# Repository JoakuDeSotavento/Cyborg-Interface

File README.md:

# InCY, INTERFACE CYBORG

## aka Jakinator

## physical interface for transforming the human body in the interface itself

## Team

### JOAQUÍN ROBERTO DÍAZ DURÁN

> PhD Researcher at Universidad Carlos III de Madrid

### MARTA TIMÓN

> M.C.S.

### PEDRO LÓPEZ

> Ing. En Electrónica

> Joakinator beta

Key Words
Interfaz corporal, Arte Ciborg, Performance, Propiocepción, Adaptar la tecnología al artista, dialogo con el otro, HCI

Joakinator is an interaface devoted to convert the languaje and signs of the human body in the interface itslef. The idea behind Joakinator is giving direct control of the multimedia elements to the artist, but this elements are not just controlled by the artist, in fact the artist also receive cues from the system. Joakinator will be a creative assistant in the creation proces of a performance.

## Skematics

## Code

## CAD DESIGN

## Getting started

Protocolo de conexión Joakinator

1. Abrir el hostspot del teléfono
2. Conectar las computadoras al hostspot y revisar su dirección IP
3. Configurar el archivo secrets.h y la parte de las direcciones IP en el programa de Arduino
4. Cargar las modificaciones al Arduino del Joakinator
5. Desconectar el cable USB y colocar las baterías. Esperar a que el led amarillo se encienda, eso significa que se ha conectado a la WLAN
6. Abrir el programa de Processing y ejecutarlo
   a. Barras blancas son las señales del Joakinator
   b. Las barras naranjas son las señales del Wekinator
7. Ver que las barras blancas vibren, si no es así resetear el Joakinator
8. Abrir Wekinator Input_helper
   a. Comprobar los puertos
9. Abrir Wekinator
   a. Comprobar los puertos
10. Abrir MAX/MSP

Protocolo de montaje del Joakinator en cuerpo

1. Seleccionar el musculo sobre el que se montara el electrodo
2. Identificar la parte central del musculo y la parte distal
3. Limpiar con alcohol o agua oxigenada las tres áreas donde se colocarán los electrodos
4. Colocar los tres electrodos en sus posiciones
   a. Rojo es la referencia
   b. Amarillo es el middle muscle
   c. Verde es el end muscle
5. Colocar la referencia general, el electrodo de un solo plug
6. Colocar los cables con los sensores flexiforce
7. Calibrar la sensibilidad de los flexiforce con los knobs
   Nota. Los Jack del lado grande del Joakinator son para los electrodos y los que están con lo knobs son para los flexiforce

## Performance using Joakinator

<div align="center">
  
</div>

> El equilibrio reside en 3 puntos
> Festival Ctrl Art Supr, Madrid, Marzo, 2019

- [Link](https://arterobotico.com/el-equilibrio-reside-en-3-puntos/)

<div align="center">
  
</div>

> Interfaz Cyborg para reflexionar la tecnología
> Encuentro Si fuese Tú, Facultad de Bellas Artes de Cuenca, UCLM, Abril, 2019

- [Link](https://arterobotico.com/interfaz-ciborg-para-reflexionar-la-tecnologia/)

## Agradecimientos

- Suported by BODYinTRANSIT Sensory-driven Body Transformation Experiences On-the-move, MagicShoes and i_mBODY Lab at UC3M.
- With the collaboration of FUZZYGAB.4. UCLM
- Project developed with the funding of CONACYT-FINBA. México; Medialab-Matadero. España."

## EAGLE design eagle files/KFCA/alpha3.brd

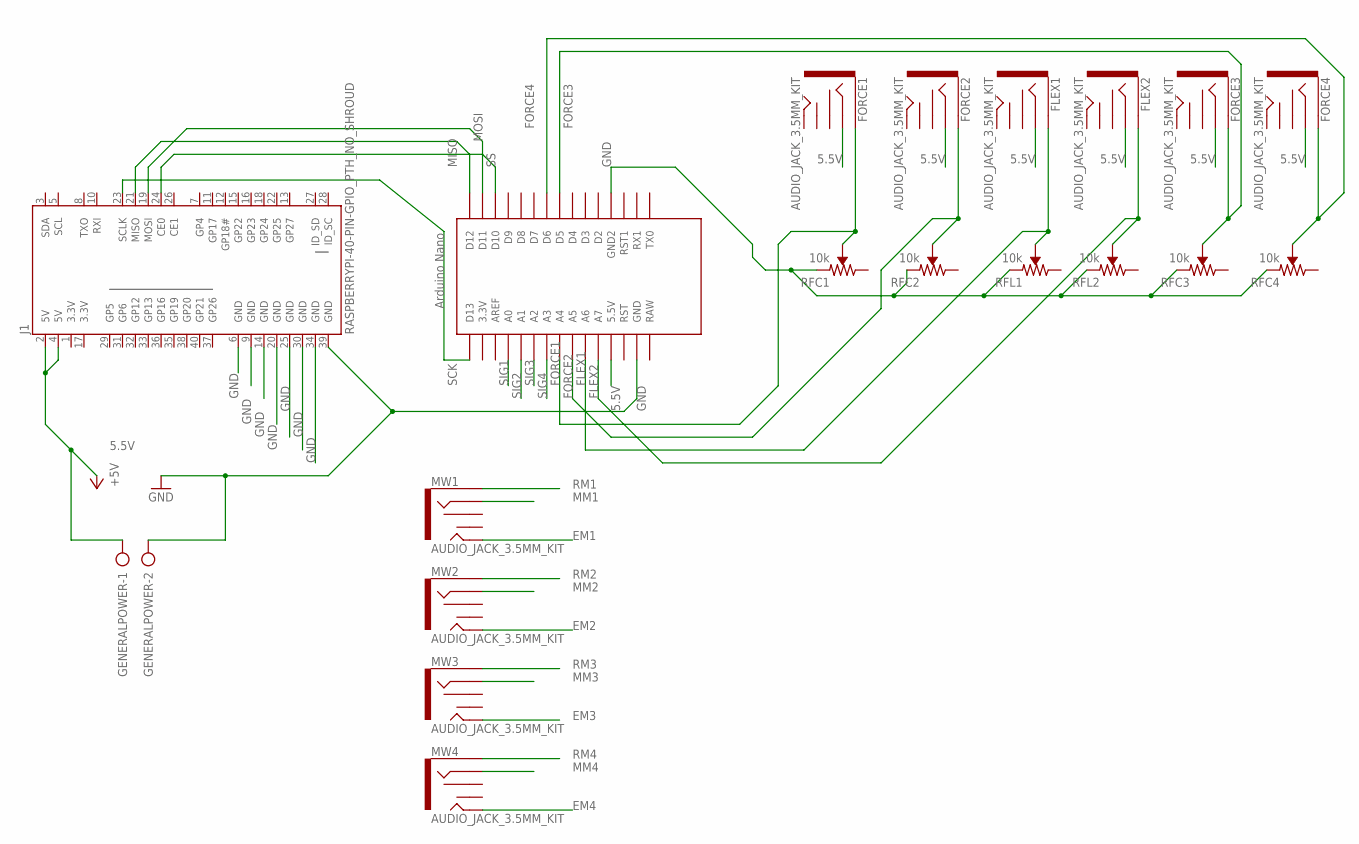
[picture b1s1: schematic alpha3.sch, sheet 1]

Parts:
FLEX1, FLEX2: AUDIO_JACK_3.5MM_KIT; AUDIO-JACK-KIT
FORCE1, FORCE2, FORCE3, FORCE4: AUDIO_JACK_3.5MM_KIT; AUDIO-JACK-KIT
GENERALPOWER: AK500/2
J1: RASPBERRYPI-40-PIN-GPIO_PTH_NO_SHROUD; 2X20
MW1, MW2, MW3, MW4: AUDIO_JACK_3.5MM_KIT; AUDIO-JACK-KIT
RFC1, RFC2, RFC3, RFC4: 10k; TRIMPOT-PTH-3386U
RFL1, RFL2: 10k; TRIMPOT-PTH-3386U
U$1: NANO

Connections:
3.3V: J1.1 (3.3V), J1.17 (3.3V)
5.5V: FLEX1.RING, FLEX2.RING, FORCE1.RING, FORCE2.RING, FORCE3.RING, FORCE4.RING, GENERALPOWER.1, J1.2 (5V), J1.4 (5V), U$1.5V (5.5V); also elsewhere on the board
EM1: MW1.TIP; also elsewhere on the board
EM2: MW2.TIP; also elsewhere on the board
EM3: MW3.TIP; also elsewhere on the board
EM4: MW4.TIP; also elsewhere on the board
FLEX1: FLEX1.SLEEVE, RFL1.2 (WIPER), U$1.A6
FLEX2: FLEX2.SLEEVE, RFL2.2 (WIPER), U$1.A7
FORCE1: FORCE1.SLEEVE, RFC1.2 (WIPER), U$1.A4
FORCE2: FORCE2.SLEEVE, RFC2.2 (WIPER), U$1.A5
FORCE3: FORCE3.SLEEVE, RFC3.2 (WIPER), U$1.D5
FORCE4: FORCE4.SLEEVE, RFC4.2 (WIPER), U$1.D6
GND: GENERALPOWER.2, J1.6 (GND), J1.9 (GND), J1.14 (GND), J1.20 (GND), J1.25 (GND), J1.30 (GND), J1.34 (GND), J1.39 (GND), RFC1.1 (CCW), RFC2.1 (CCW), RFC3.1 (CCW), RFC4.1 (CCW), RFL1.1 (CCW), RFL2.1 (CCW), U$1.GND, U$1.GND1 (GND2); also elsewhere on the board
MISO: J1.21 (MISO), U$1.D12
MM1: MW1.RING; also elsewhere on the board
MM2: MW2.RING; also elsewhere on the board
MM3: MW3.RING; also elsewhere on the board
MM4: MW4.RING; also elsewhere on the board
MOSI: J1.19 (MOSI), U$1.D11
RM1: MW1.SLEEVE; also elsewhere on the board
RM2: MW2.SLEEVE; also elsewhere on the board
RM3: MW3.SLEEVE; also elsewhere on the board
RM4: MW4.SLEEVE; also elsewhere on the board
SCK: J1.23 (SCLK), U$1.D13
SIG1: U$1.A0; also elsewhere on the board
SIG2: U$1.A1; also elsewhere on the board
SIG3: U$1.A2; also elsewhere on the board
SIG4: U$1.A3; also elsewhere on the board
SS: J1.24 (CE0), U$1.D10

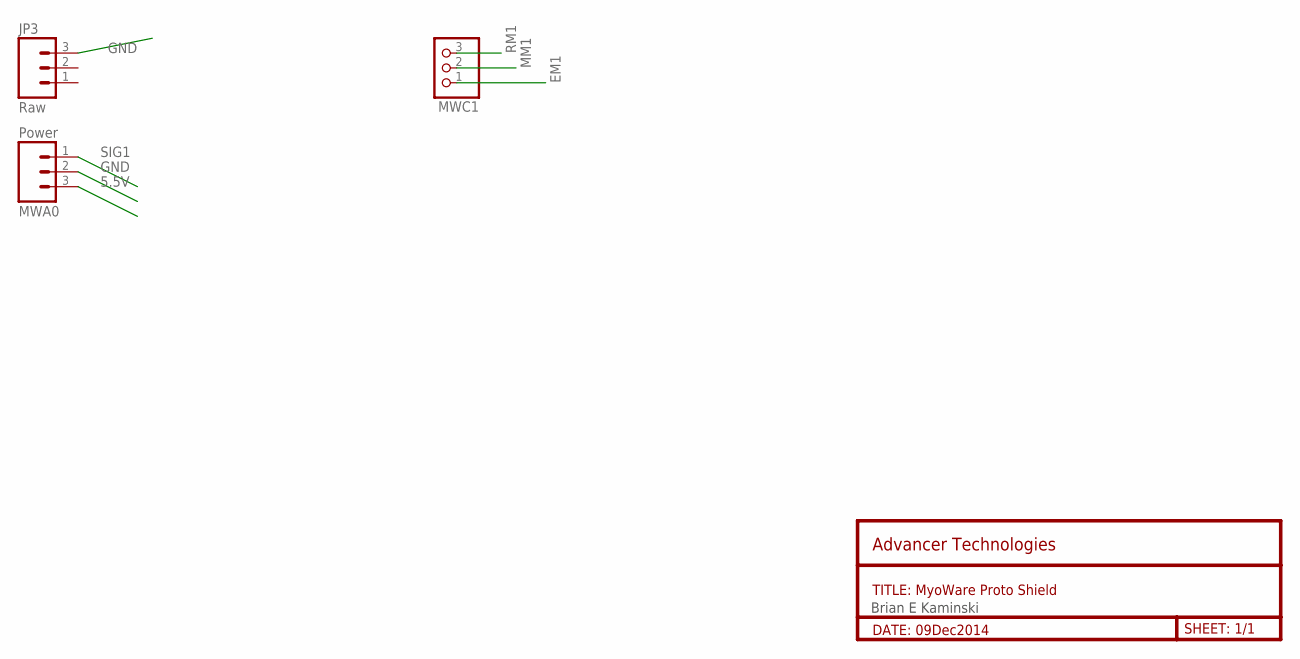
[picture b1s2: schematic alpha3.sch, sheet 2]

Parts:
JP3: Raw; 1X03_NO_SILK
MWA0: Power; 1X03_NO_SILK
MWC1: PINHD-1X3; 1X03

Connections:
5.5V: MWA0.3; also elsewhere on the board
EM1: MWC1.1; also elsewhere on the board
GND: JP3.3, MWA0.2; also elsewhere on the board
MM1: MWC1.2; also elsewhere on the board
RM1: MWC1.3; also elsewhere on the board
SIG1: MWA0.1; also elsewhere on the board

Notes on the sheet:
Brian E Kaminski
TITLE: MyoWare Proto Shield
DATE: 09Dec2014
SHEET: 1/1
Advancer Technologies

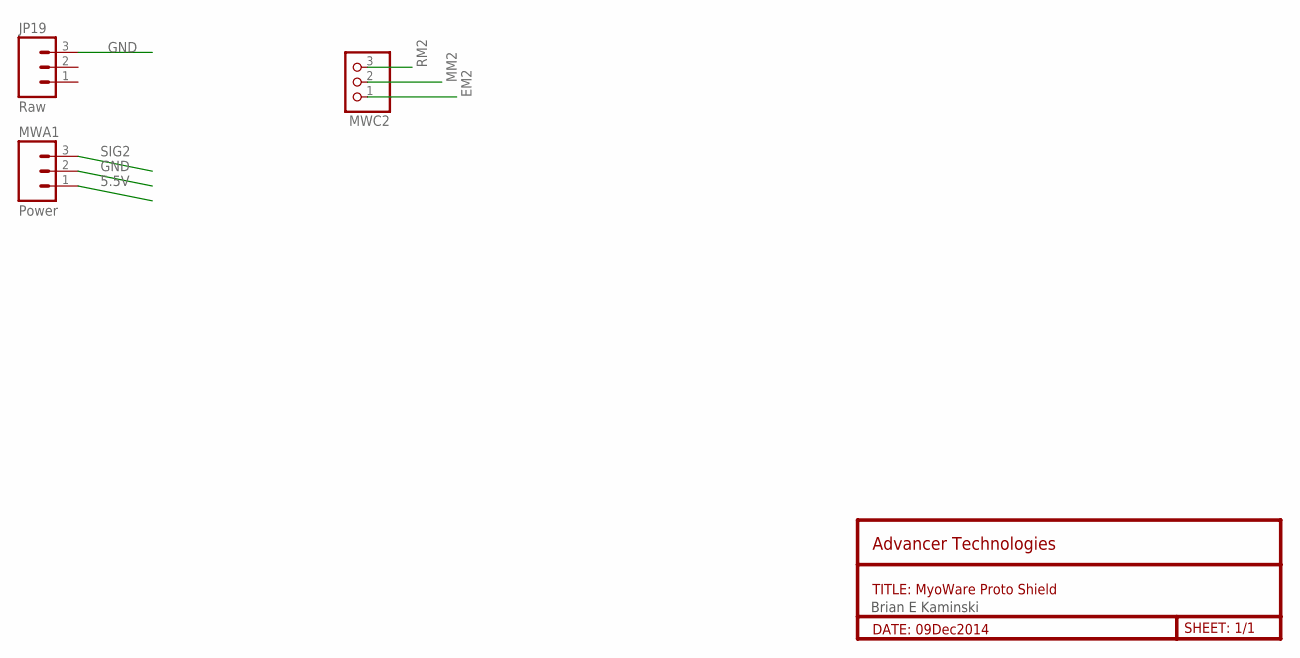
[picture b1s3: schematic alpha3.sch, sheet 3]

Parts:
JP19: Raw; 1X03_NO_SILK
MWA1: Power; 1X03_NO_SILK
MWC2: PINHD-1X3; 1X03

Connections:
5.5V: MWA1.1; also elsewhere on the board
EM2: MWC2.1; also elsewhere on the board
GND: JP19.3, MWA1.2; also elsewhere on the board
MM2: MWC2.2; also elsewhere on the board
RM2: MWC2.3; also elsewhere on the board
SIG2: MWA1.3; also elsewhere on the board

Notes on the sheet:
Brian E Kaminski
TITLE: MyoWare Proto Shield
DATE: 09Dec2014
SHEET: 1/1
Advancer Technologies

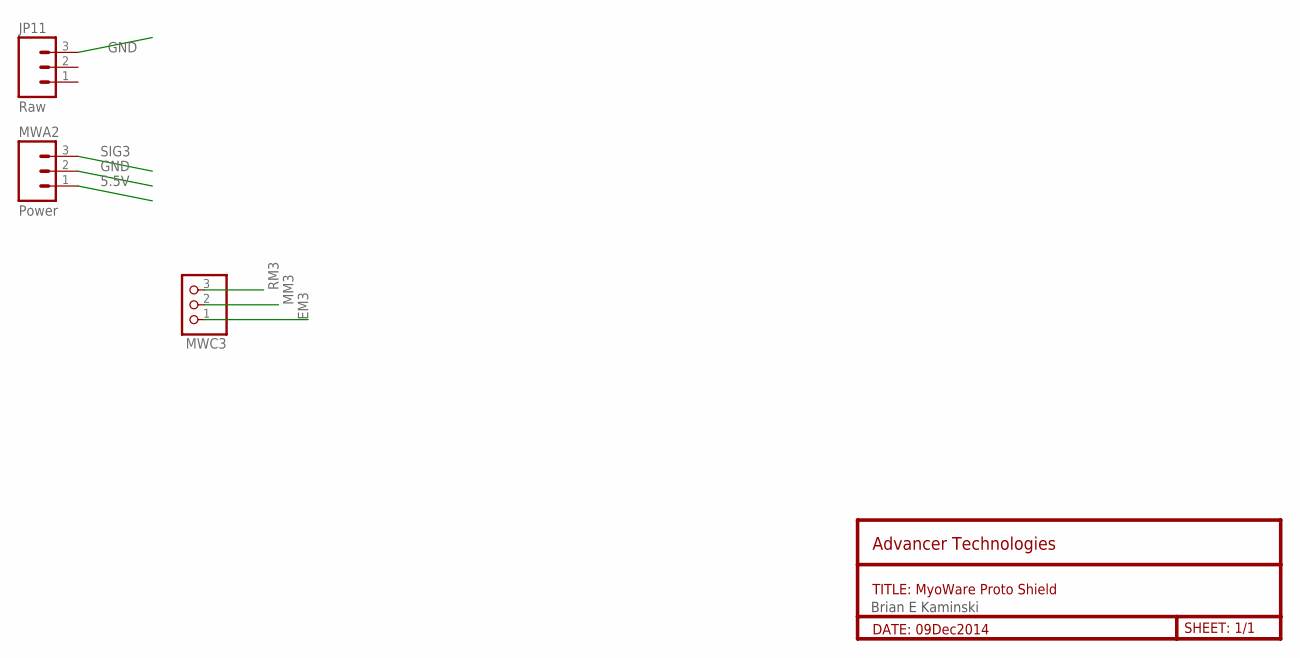
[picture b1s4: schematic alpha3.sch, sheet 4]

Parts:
JP11: Raw; 1X03_NO_SILK
MWA2: Power; 1X03_NO_SILK
MWC3: PINHD-1X3; 1X03

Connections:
5.5V: MWA2.1; also elsewhere on the board
EM3: MWC3.1; also elsewhere on the board
GND: JP11.3, MWA2.2; also elsewhere on the board
MM3: MWC3.2; also elsewhere on the board
RM3: MWC3.3; also elsewhere on the board
SIG3: MWA2.3; also elsewhere on the board

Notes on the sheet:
Brian E Kaminski
TITLE: MyoWare Proto Shield
DATE: 09Dec2014
SHEET: 1/1
Advancer Technologies

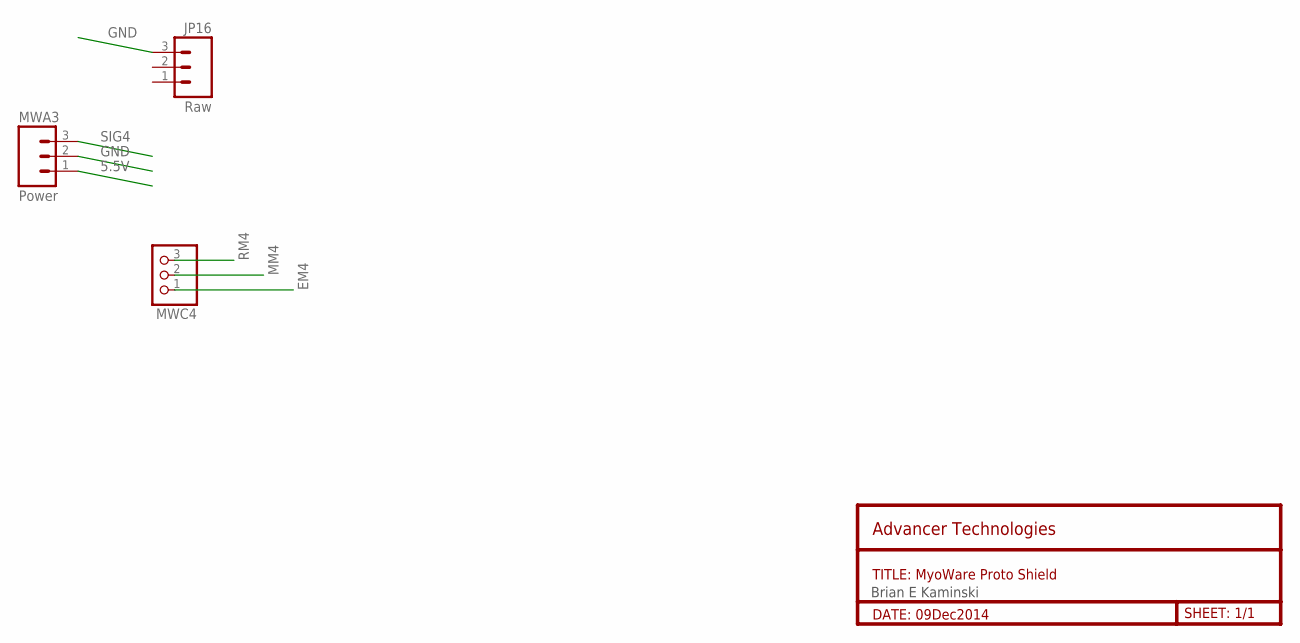
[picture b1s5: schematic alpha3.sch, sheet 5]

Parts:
JP16: Raw; 1X03_NO_SILK
MWA3: Power; 1X03_NO_SILK
MWC4: PINHD-1X3; 1X03

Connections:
5.5V: MWA3.1; also elsewhere on the board
EM4: MWC4.1; also elsewhere on the board
GND: JP16.3, MWA3.2; also elsewhere on the board
MM4: MWC4.2; also elsewhere on the board
RM4: MWC4.3; also elsewhere on the board
SIG4: MWA3.3; also elsewhere on the board

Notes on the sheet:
Brian E Kaminski
TITLE: MyoWare Proto Shield
DATE: 09Dec2014
SHEET: 1/1
Advancer Technologies

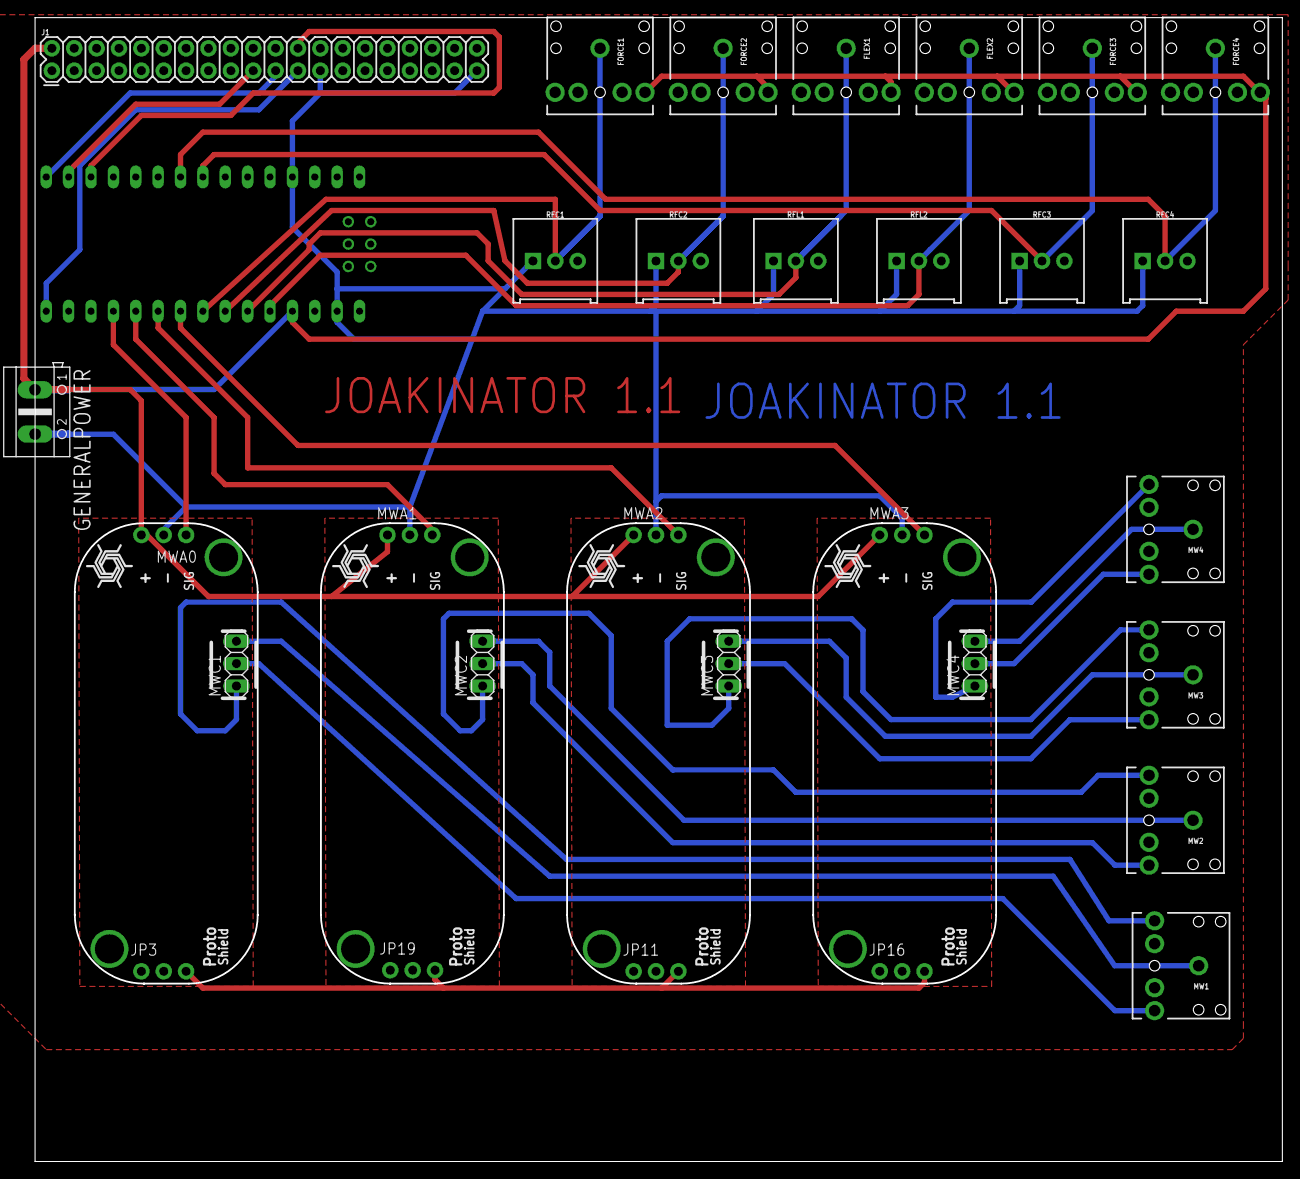
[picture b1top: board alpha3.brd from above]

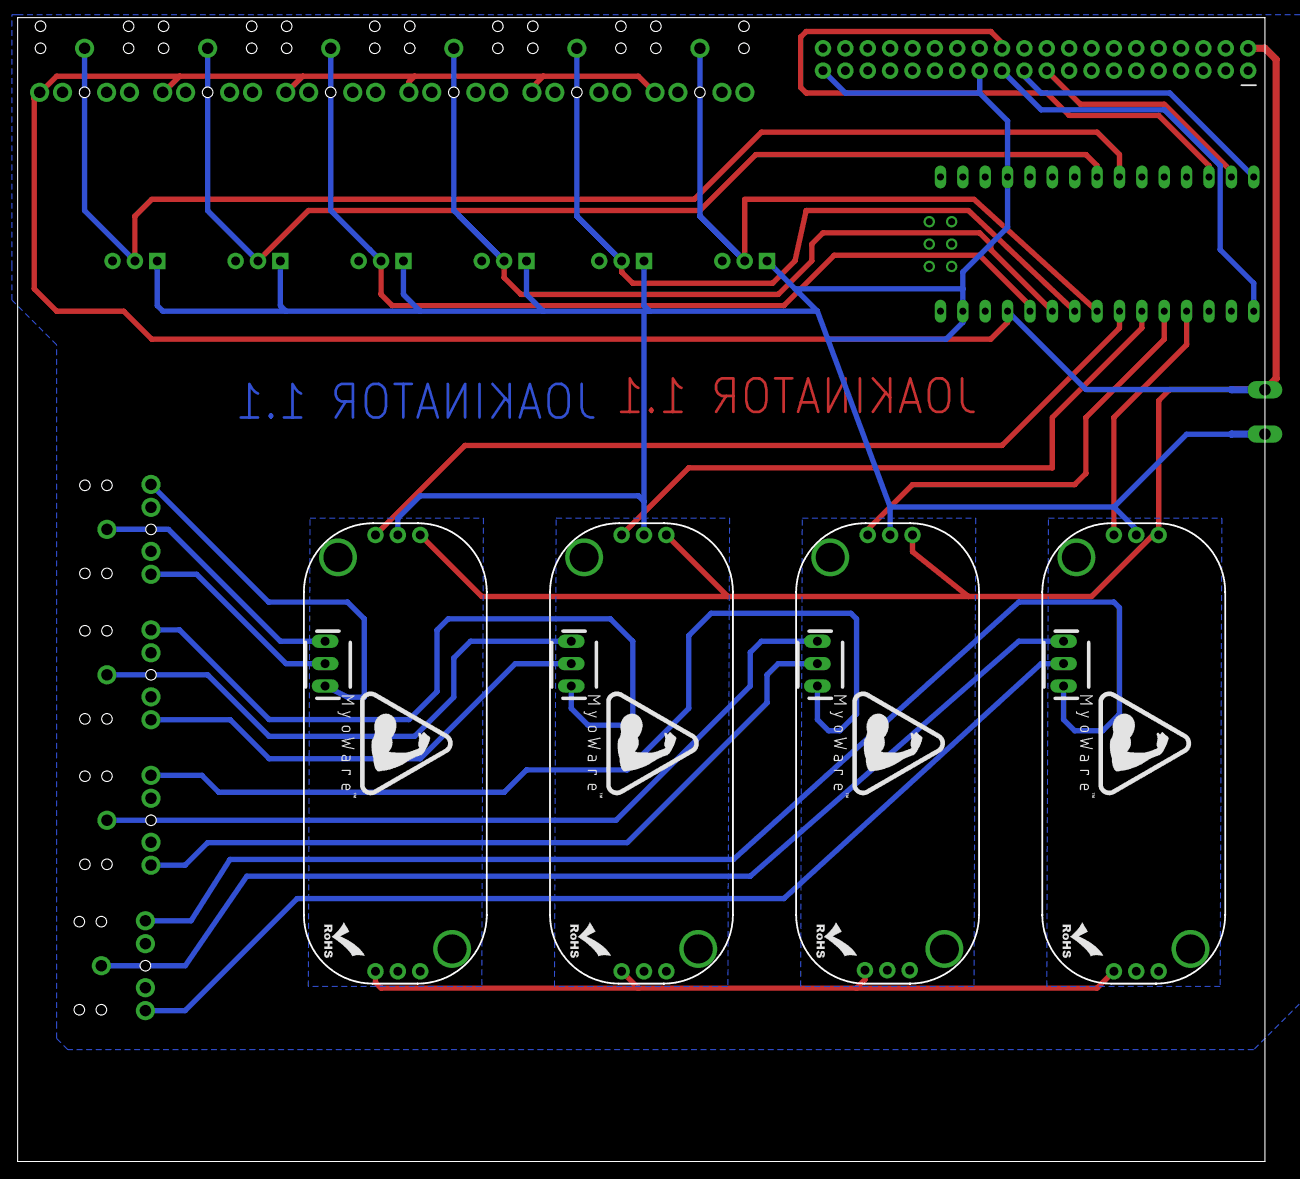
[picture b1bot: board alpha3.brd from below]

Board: 2 copper layers, 141.6 x 129.8 mm, 43 parts (8 on the bottom side), 29 nets.

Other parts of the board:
U$2, U$8, U$13, U$17: MYOWARE_LOGO
U$3, U$6, U$11, U$15: ROHS
U$7, U$9, U$12, U$16: SPIRAL_LOGO_60%

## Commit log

2019-05-18 Images
    Images for the readme file
2019-06-05 se agrego el Eagle
2019-08-10 Primeras partes
2019-08-10 nuevo de max
2019-08-10 todo en orden
    para hacer la prueba del roling window
2019-08-11 Libraries
2019-08-15 trabajo en max
2019-08-15 uno mas de arduino
2019-08-18 Algunos experimentos en MAX
    Estoy intentanto visualizar la señal de la INTCY en MAX
2019-08-19 nuevo datos weki rolling wondow
2019-10-08 cambios realizados en Donosti
2019-11-28 El OSC mkr1010 de arduino funciona bien
    El problema era en la IP de salida, habia que ponerla directa
2019-11-28 Avances en el MKR
2019-11-30 ultimo update
2019-11-30 un poco de seguridad
2019-11-30 super security
2019-11-30 added circular buffer to analog inputs 0 and 1
2019-12-25 Todos los cambios hasta Donostia-Tabakalera
    Este incluye el diseño del case, los diseños del circuito.
    Incluye los entrenamientos del wekinator con Fran
    Las ultimas actualizaciones de Arduino, Processing
    Incluye un Patch sensillo del Audio Scratx
2020-02-18 ensayo 18 febrero 2020
2020-02-20 arreglos para la colaboracion con Pablo
    Usamos el objeto Karma~ para hacer la maquina looper y poco mas.
    El trabajo de esta parte fué adaptar el Wekinator a Karma~.
2020-02-25 Ensayos con Pablo
    Diseño completo de una pieza de Audio para la performance.
2020-03-27 Last comit
2020-09-15 Avances de la tesis
2020-10-19 Ultima actualkizacion
2021-06-07 un ano en un dia
2021-10-22 Ultima actualización funcional
2021-10-23 proyecto max
2021-10-23 apendificador y patch
2021-10-23 appendifications
2021-10-23 muchos cambios de archivos
2021-10-24 Minimo cambio
2021-10-24 Arreglando el audio
2021-10-24 Listo el audio
    Avance de la interfaz performativa
2021-10-30 Ultima actualizacion antes de la defensa
    Todo el setup listo
2022-01-21 Cambios para la performance de La Isla
2022-02-10 Joakinator Reloaded
2022-02-10 Reorganización con taller complu
2022-02-10 Taller Complu
2022-02-10 Taller Complu 2
2022-03-21 Cambios con pablito
2022-04-05 Trabajo con Karma
2022-04-06 Ensayo elementos
2022-04-14 Arreglos parciales del Parch para la performance
2022-04-14 Trabajando con karma buen avance
2022-04-20 Ensayo looper
2022-04-21 Organizacion
2022-04-21 Organizacion this is not
2022-04-25 PERFO LAB
2022-04-25 Finde
2022-04-27 merge
2022-04-27 Megrge 2
2022-05-02 Perfo en pradillo
2022-05-02 Puesta en orden
2022-05-09 Latice
2022-05-13 perfo en 4KKK
2022-05-13 Matadero Lattice
2022-05-16 Perfo Lattice La Isla
2022-05-23 Laticce Molino lab
2022-06-22 Performance en Berlín
2022-07-30 Navelart
2022-09-05 Ultimo cambio de posibles presentes
2022-09-09 Ultimo ensayo antes de umbral
2022-09-14 Last perfo at Umbral
2022-10-08 Hack Meeting
2022-10-22 Il Soplo advances
2022-11-02 Lattice Factoria Jarana
2022-12-19 Taller de embodyment
2023-02-10 Perfo Bologna y i_mBODY Lab
2023-02-10 Readme in taller complutence and main readme
2023-02-10 readme update
2023-03-31 bologna
2023-06-08 Ajustes de limpieza
2023-10-27 El primer tacto
2023-10-28 Lattice Seara
2024-05-16 update for mocap
2024-05-17 Biophony
2024-05-29 estado despues de biophonics
2024-09-18 actualizaion en chile
2024-10-28 Chile Update
2025-02-20 Project Olas

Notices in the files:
parts and their libraries:
SparkFun-Connectors: Licensing: Creative Commons ShareAlike 4.0 International - https://creativecommons.org/licenses/by-sa/4.0
